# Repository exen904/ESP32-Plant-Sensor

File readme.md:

# ESP-32 Plant Sensor for ESP-Home and HomeAssistant

This is a simple PCB to attach 6 capacitive moisuture sensors to a ESP32 for plant monitoring in HomeAssistant. The available MiFlora and Tuya clones with Zigbee were to expensive to purchase for all of my plants, so I chose this way. 

The PCB works with both V1.2 and V2.0 sensors and applys 5V as working voltage to make it compatible with either one. Connection to the sensors is made via JST 2.0 connectors. 

## Update
PCB has been updated to accomodate larger tolerances on the ESP footprint THT holes. My first protoytpe showed no errors, but I could confirm, that the tolerances on the THT holes are extremely tight. I adjusted this in the current version, so if you did not order PCBs, please use the current version. If you ordered PCBs from the first revision, you can take a chance at drilling the holes up but I dont really recommend that, as you can also break traces during that. 

## ESP Pinout
Please refer to my KiCad Footprint of the ESP I used for the pinout, as there are so many different ESP Devkits available. 

## BOM
- 1x ESP32 Devkit with the correct pinout
- 6x JST B3B-XH-A (2.0mm vertical) connectors
- 4x M2x4 screws for securing the PCB in the bottom case

## Software
I run these with ESPHome, see my code in the code folder. Calibrate the values under `calibrate_linear` for each state of sensor dry and sensor 100% (sensor partly emerged underwater).

For the HomeAssistant side of things, I created a configuration.yaml entry, which ties each sensor to a plant entity. Example also linked in the code folder. Please do yourself a favour, and name your sensors in ESPHome better than I did.

## Pictures

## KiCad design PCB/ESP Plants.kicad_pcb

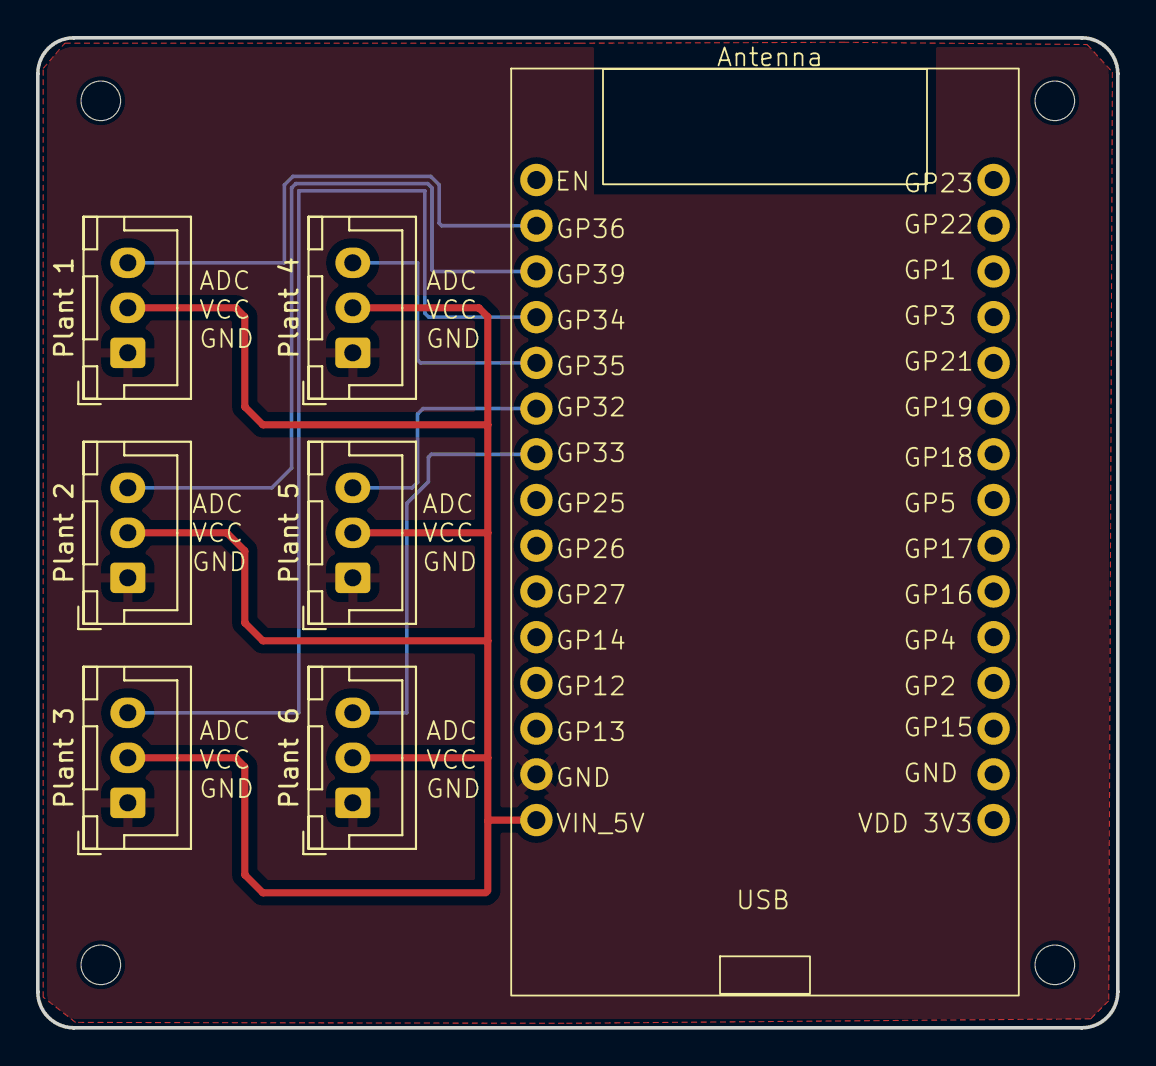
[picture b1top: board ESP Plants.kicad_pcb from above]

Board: 2 copper layers, 60.0 x 55.0 mm, 7 parts (0 on the bottom side), 8 nets.

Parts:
NodeMCU_32S1: ESP32_NodeMCU
Plant 1, Plant 2, Plant 3, Plant 4, Plant 5, Plant 6: Conn_01x03_Pin; JST_XH_B3B-XH-A_1x03_P2.50mm_Vertical

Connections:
/ADC1: NodeMCU_32S1.14 (GPIO36/ADC0), Plant 1.3
/ADC2: NodeMCU_32S1.13 (GPIO39/ADC3), Plant 2.3
/ADC3: NodeMCU_32S1.12 (GPIO34/ADC6), Plant 3.3
/ADC4: NodeMCU_32S1.11 (GPIO35/ADC7), Plant 4.3
/ADC5: NodeMCU_32S1.10 (GPIO32/ADC4/TOUCH9), Plant 5.3
/ADC6: NodeMCU_32S1.9 (GPIO33/ADC5/TOUCH8), Plant 6.3
/GND: NodeMCU_32S1.2 (GND), Plant 1.1, Plant 2.1, Plant 3.1, Plant 4.1, Plant 5.1, Plant 6.1
/VCC: NodeMCU_32S1.1 (VIN_5V), Plant 1.2, Plant 2.2, Plant 3.2, Plant 4.2, Plant 5.2, Plant 6.2

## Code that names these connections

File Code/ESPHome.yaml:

# your regular ESPHome configuration gets here, stuff for the sensors follows

sensor:
#Sensor 1
  - platform: adc
    attenuation: auto
    pin: GPIO036
    name: "Sensor 1"
    device_class: moisture
    update_interval: 120s
    unit_of_measurement: "%"
    filters:
    - median:
        window_size: 7
        send_every: 4
        send_first_at: 1
    - calibrate_linear:
        - 2.3 -> 0.00
        - 0.9 -> 100.00
    - lambda: if (x < 1) return 0; else return (x);
    accuracy_decimals: 0 


#Sensor 2    
  - platform: adc
    attenuation: auto
    pin: GPIO39
    name: "Sensor 2"
    device_class: moisture
    update_interval: 120s
    unit_of_measurement: "%"
    filters:
    - median:
        window_size: 7
        send_every: 4
        send_first_at: 1
    - calibrate_linear:
        - 2.3 -> 0.00
        - 0.9 -> 100.00
    - lambda: if (x < 1) return 0; else return (x);
    accuracy_decimals: 0 


#Sensor 3    
  - platform: adc
    attenuation: auto
    pin: GPIO34
    name: "Sensor 3"
    device_class: moisture
    update_interval: 120s
    unit_of_measurement: "%"
    filters:
    - median:
        window_size: 7
        send_every: 4
        send_first_at: 1
    - calibrate_linear:
        - 2.4 -> 0.00
        - 0.9 -> 100.00
    - lambda: if (x < 1) return 0; else return (x);
    accuracy_decimals: 0   
 

#Sensor 4    
  - platform: adc
    attenuation: auto
    pin: GPIO35
    name: "Sensor 4"
    device_class: moisture
    update_interval: 120s
    unit_of_measurement: "%"
    filters:
    - median:
        window_size: 7
        send_every: 4
        send_first_at: 1
    - calibrate_linear:
        - 2.4 -> 0.00
        - 0.9 -> 100.00
    - lambda: if (x < 1) return 0; else return (x);
    accuracy_decimals: 0   

#Sensor 5    
  - platform: adc
    attenuation: auto
    pin: GPIO32
    name: "Sensor 5"
    device_class: moisture
    update_interval: 120s
    unit_of_measurement: "%"
    filters:
    - median:
        window_size: 7
        send_every: 4
        send_first_at: 1
    - calibrate_linear:
        - 2.4 -> 0.00
        - 0.9 -> 100.00
    - lambda: if (x < 1) return 0; else return (x);
    accuracy_decimals: 0   

    #Sensor 6    
  - platform: adc
    attenuation: auto
    pin: GPIO33
    name: "Sensor 6"
    device_class: moisture
    update_interval: 120s
    unit_of_measurement: "%"
    filters:
    - median:
        window_size: 7
        send_every: 4
        send_first_at: 1
    - calibrate_linear:
        - 2.4 -> 0.00
        - 0.9 -> 100.00
    - lambda: if (x < 1) return 0; else return (x);
    accuracy_decimals: 0   

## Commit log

2024-11-07 added case files and updated readme
2024-11-07 img resize
2024-11-07 license
2024-11-07 added pinout to readme
2024-11-07 BOM updated
2024-11-25 add device class to esphome sensor
2024-11-25 THT holes on ESP footprint editet for better tolerances
2024-11-25 updated production files to new THT holes
2024-11-25 updated readme to current PCB revision
